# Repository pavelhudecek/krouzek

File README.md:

Na práci s GITem si nainstalujte
    https://git-scm.com/downloads/win

Když už máte git nainstalován,
1. Založte si nějaký adresář, kam se bude repozitář z gitu klonovat, např. C:\Users\mojejmeno\Documents\git-krouzek-elektro
2. Otevřete příkazový terminál, pokud ho nemáte už přidanej ve start menu, dejte hledat cmd.
3. Příkazem cd jít do toho adresáře:
   cd C:\Users\mojejmeno\Documents\git-krouzek-elektro (a stisk enter)
4. git clone https://github.com/pavelhudecek/krouzek.git (a stisk enter)

Microchip Studio a jak začít:
https://dejvice.cz/edison/krouzek/at-st/

Kromě Microchip Studia můžete použít třeba VScode:
https://code.visualstudio.com/download
Ale je poněkud univerzálnější, takže je potřeba doinstalovat vhodné pluginy a podobně.

Na nahrávání programu bez Microchip Studia použijte např.:
https://blog.zakkemble.net/avrdudess-a-gui-for-avrdude/

Nebo si můžete do VScode nastavit nahrávání přes avrdude:
    https://github.com/mariusgreuel/avrdude/releases 

Dále je dobré si pořídit terminál pro komunikaci. V nejhorším se dá použít i integrovaný v Microchip Studiu, ale radši třeba YAT:
    https://sourceforge.net/projects/y-a-terminal/
    V některých projektech najdete soubor s příponou .yat, tam je nastavení pro daný projekt, stačí nahrát, jen bude asi potřeba změnit číslo portu.

Poznámka: Na kroužku to vypadalo, že z Microchip Studia nejde nahrávat program přes Xnano416 do ATtiny814, ale zdá se, že se jedná jen o větší citlivost na běžící repráček, nebo rychlý blikání. Jinak to normálně jde:-)

https://dejvice.cz/edison/tmp/ibom.html

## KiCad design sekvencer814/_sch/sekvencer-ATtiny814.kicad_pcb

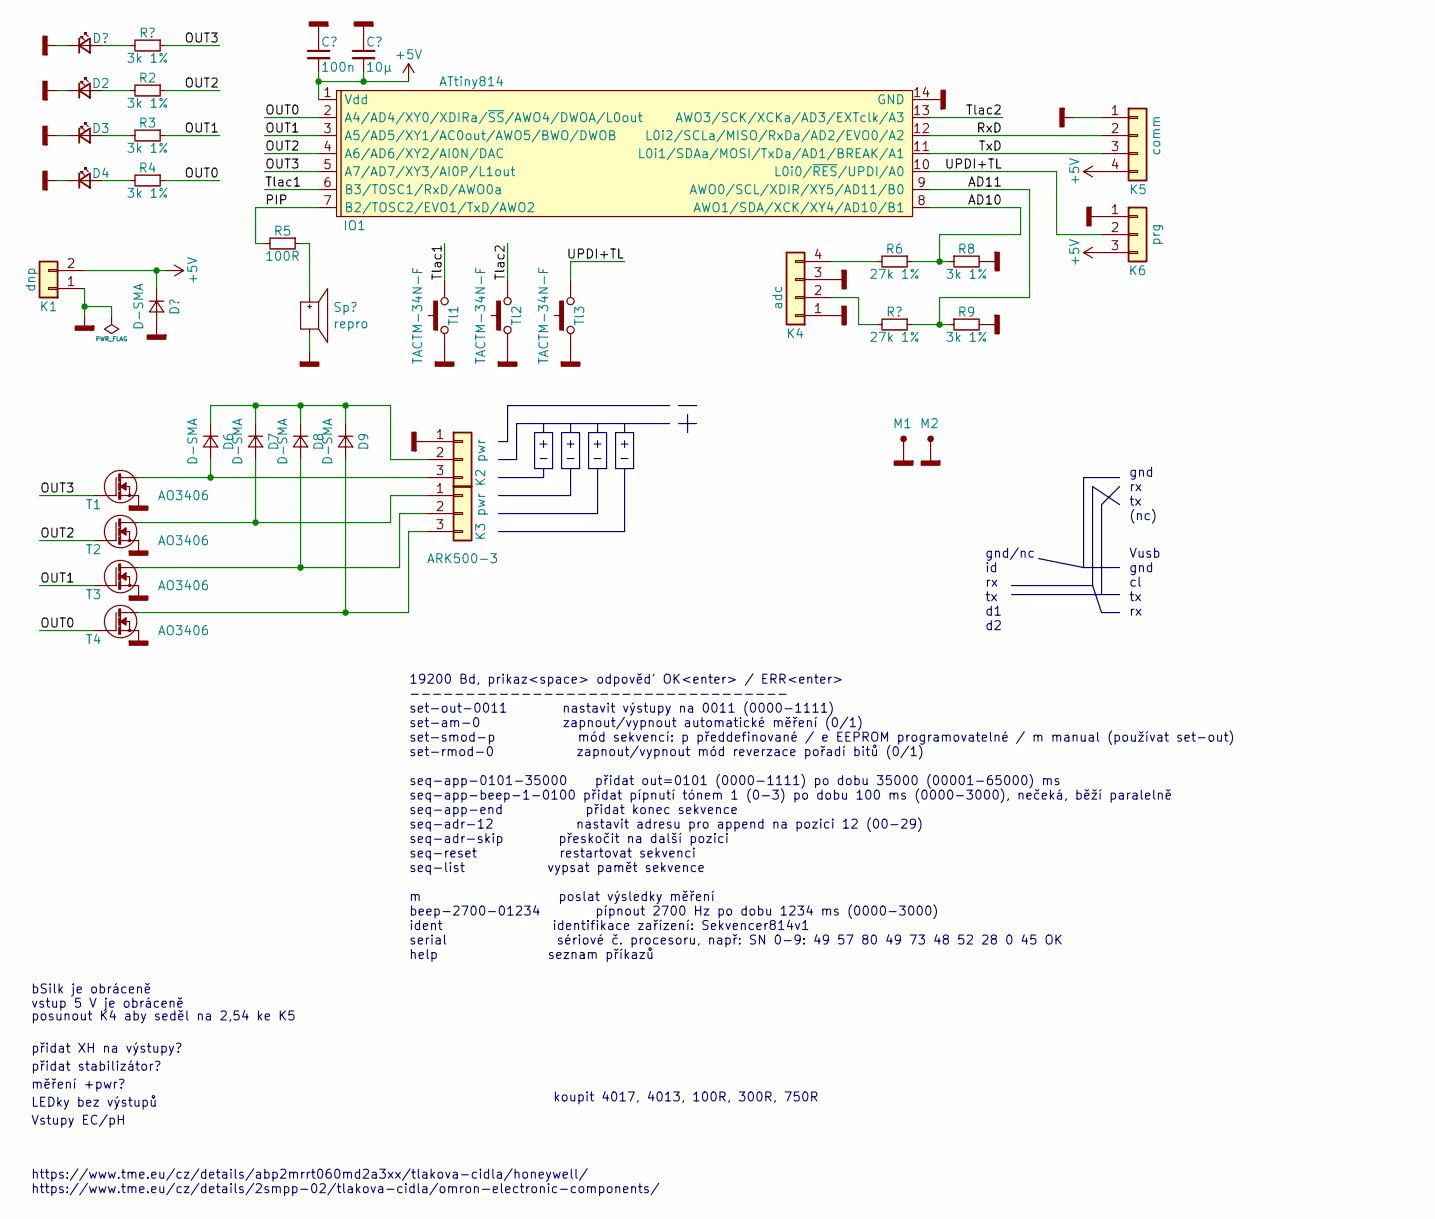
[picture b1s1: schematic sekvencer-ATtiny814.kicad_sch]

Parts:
C1: 100n; R_1206-hand
C2: 10µ; R_1206-hand
D1, D2, D3, D4: R; LED1206-hand
D5, D6, D7, D8, D9: D-SMA; D-SMA-hand
IO1: ATtiny814; SO14-hand
K1: dnp; kon-1x2-s2x4+holes-pwr
K2, K3: ARK500-3
K4, K5: dnp; kon-1x4-D1-1,7
K6: dnp; kon-1x3_P2.54_Vertical
M1, M2: dnp; PTH-M3-7.5
R1, R2, R3, R4, R8, R9: 3k 1%; R_1206-hand
R5: 100R; R_1206-hand
R6, R7: 27k 1%; R_1206-hand
Sp1: repro; repro-D12-RM6.5-pol
T1, T2, T3, T4: AO3406; SOT23-hand
Tl1, Tl2, Tl3: TACTM-34N-F; TD-03-hand

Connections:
+5V: C1.2, C2.2, D5.1 (K), IO1.1 (Vdd), K1.2, K5.4, K6.3
/AD10: IO1.8 (AWO1/SDA/XCK/XY4/AD10/B1), R6.1, R8.1
/AD11: IO1.9 (AWO0/SCL/XDIR/XY5/AD11/B0), R7.1, R9.1
/OUT0: IO1.2 (A4/AD4/XY0/XDIRa/~SS/AWO4/DWOA/L0out), R4.1, T4.1 (G)
/OUT1: IO1.3 (A5/AD5/XY1/AC0out/AWO5/BWO/DWOB), R3.1, T3.1 (G)
/OUT2: IO1.4 (A6/AD6/XY2/AI0N/DAC), R2.1, T2.1 (G)
/OUT3: IO1.5 (A7/AD7/XY3/AI0P/L1out), R1.1, T1.1 (G)
/PIP: IO1.7 (B2/TOSC2/EVO1/TxD/AWO2), R5.2
/RxD: IO1.12 (L0i2/SCLa/MISO/RxDa/AD2/EVO0/A2), K5.2
/Tlac1: IO1.6 (B3/TOSC1/RxD/AWO0a), Tl1.2
/Tlac2: IO1.13 (AWO3/SCK/XCKa/AD3/EXTclk/A3), Tl2.2
/TxD: IO1.11 (L0i1/SDAa/MOSI/TxDa/AD1/BREAK/A1), K5.3
/UPDI+TL: IO1.10 (L0i0/~RES/UPDI/A0), K6.2, Tl3.2
GNDD: C1.1, C2.1, D1.1 (K), D2.1 (K), D3.1 (K), D4.1 (K), D5.2 (A), IO1.14 (GND), K1.1, K2.1, K4.1, K4.3, K5.1, K6.1, M1.1 (TP), M2.1 (TP), R8.2, R9.2, Sp1.2 (m), T1.2 (S), T2.2 (S), T3.2 (S), T4.2 (S), Tl1.1, Tl2.1, Tl3.1
unnamed: D1.2 (A), R1.2
unnamed: D2.2 (A), R2.2
unnamed: D3.2 (A), R3.2
unnamed: D4.2 (A), R4.2
unnamed: D6.2 (A), K2.3, T1.3 (D)
unnamed: D6.1 (K), D7.1 (K), D8.1 (K), D9.1 (K), K2.2
unnamed: D7.2 (A), K3.1, T2.3 (D)
unnamed: D8.2 (A), K3.2, T3.3 (D)
unnamed: D9.2 (A), K3.3, T4.3 (D)
unnamed: K4.2, R7.2
unnamed: K4.4, R6.2
unnamed: R5.1, Sp1.1 (p)

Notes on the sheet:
+ -
gnd rx tx (nc)
https://www.tme.eu/cz/details/abp2mrrt060md2a3xx/tlakova-cidla/honeywell/ https://www.tme.eu/cz/details/2smpp-02/tlakova-cidla/omron-electronic-components/
koupit 4017, 4013, 100R, 300R, 750R
vstup 5 V je obráceně
bSilk je obráceně
Vstupy EC/pH
přidat XH na výstupy?
LEDky bez výstupů
Vusb gnd cl tx rx
gnd/nc id rx tx d1 d2
přidat stabilizátor?
posunout K4 aby seděl na 2,54 ke K5
19200 Bd, prikaz<space> odpověď OK<enter> / ERR<enter> ---------------------------------- set-out-0011 nastavit výstupy na 0011 (0000-1111) set-am-0 zapnout/vypnout automatické měření (0/1) set-smod-p mód sekvencí: p předdefinované / e EEPROM programovatelné / m manual (používat set-out) set-rmod-0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
měření +pwr?

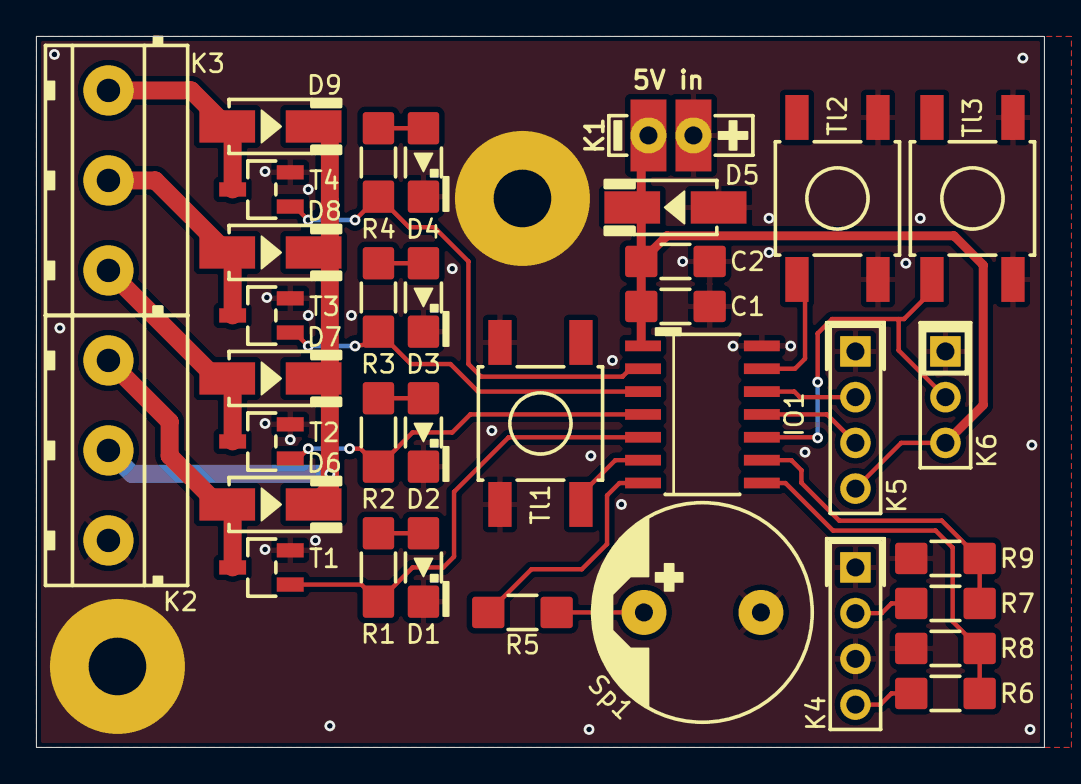
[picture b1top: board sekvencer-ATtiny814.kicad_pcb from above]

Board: 2 copper layers, 56.0 x 39.5 mm, 37 parts (0 on the bottom side), 26 nets.

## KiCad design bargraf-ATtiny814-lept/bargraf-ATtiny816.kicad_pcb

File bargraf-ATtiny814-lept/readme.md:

Kicad schéma + DPS
https://www.kicad.org/download/windows/

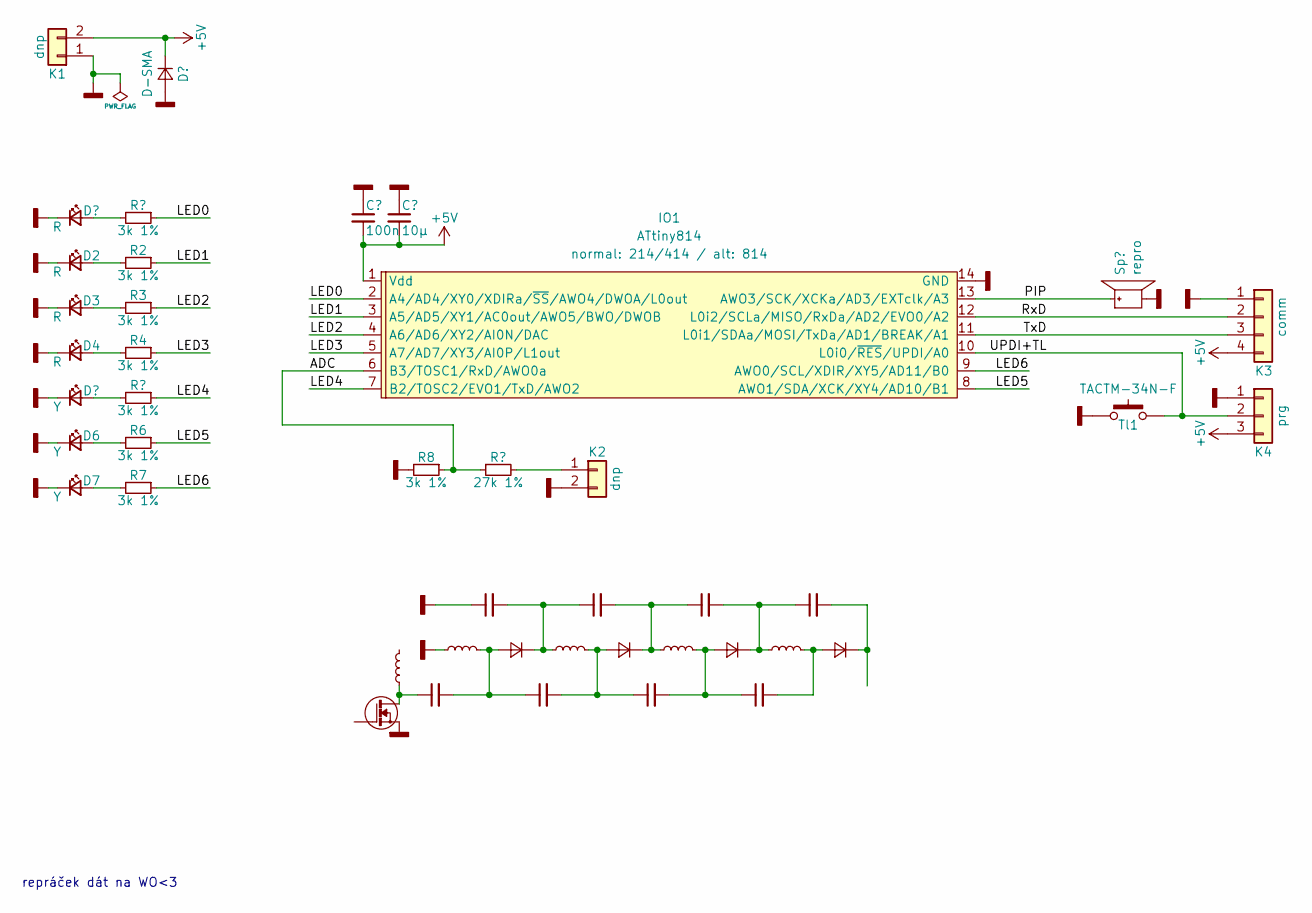
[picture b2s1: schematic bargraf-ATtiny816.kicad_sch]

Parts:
C1: 100n; R_1206-hand
C2: 10µ; R_1206-hand
D1, D2, D3, D4: R; LED1206-hand
D5, D6, D7: Y; LED1206-hand
D8: D-SMA; D-SMA-hand
IO1: ATtiny814; SO14
K1, K2: dnp; kon-1x2-s2x4
K3: dnp; kon-1x4-s1,2x3-P2
K4: dnp; kon-1x3-s2x4
R1, R2, R3, R4, R5, R6, R7, R8: 3k 1%; R_1206-hand
R9: 27k 1%; R_1206-hand
Sp1: repro; repro-D12-RM6.5-pol
Tl1: TACTM-34N-F; TD-03-hand

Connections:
+5V: C1.2, C2.2, D8.1 (K), IO1.1 (Vdd), K1.2, K3.4, K4.3
/ADC: IO1.6 (B3/TOSC1/RxD/AWO0a), R8.1, R9.1
/LED0: IO1.2 (A4/AD4/XY0/XDIRa/~SS/AWO4/DWOA/L0out), R1.1
/LED1: IO1.3 (A5/AD5/XY1/AC0out/AWO5/BWO/DWOB), R2.1
/LED2: IO1.4 (A6/AD6/XY2/AI0N/DAC), R3.1
/LED3: IO1.5 (A7/AD7/XY3/AI0P/L1out), R4.1
/LED4: IO1.7 (B2/TOSC2/EVO1/TxD/AWO2), R5.1
/LED5: IO1.8 (AWO1/SDA/XCK/XY4/AD10/B1), R6.1
/LED6: IO1.9 (AWO0/SCL/XDIR/XY5/AD11/B0), R7.1
/PIP: IO1.13 (AWO3/SCK/XCKa/AD3/EXTclk/A3), Sp1.1 (p)
/RxD: IO1.12 (L0i2/SCLa/MISO/RxDa/AD2/EVO0/A2), K3.2
/TxD: IO1.11 (L0i1/SDAa/MOSI/TxDa/AD1/BREAK/A1), K3.3
/UPDI+TL: IO1.10 (L0i0/~RES/UPDI/A0), K4.2, Tl1.2
GNDD: C1.1, C2.1, D1.1 (K), D2.1 (K), D3.1 (K), D4.1 (K), D5.1 (K), D6.1 (K), D7.1 (K), D8.2 (A), IO1.14 (GND), K1.1, K2.2, K3.1, K4.1, R8.2, Sp1.2 (m), Tl1.1
unnamed: D1.2 (A), R1.2
unnamed: D2.2 (A), R2.2
unnamed: D3.2 (A), R3.2
unnamed: D4.2 (A), R4.2
unnamed: D5.2 (A), R5.2
unnamed: D6.2 (A), R6.2
unnamed: D7.2 (A), R7.2
unnamed: K2.1, R9.2

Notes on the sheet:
repráček dát na WO<3

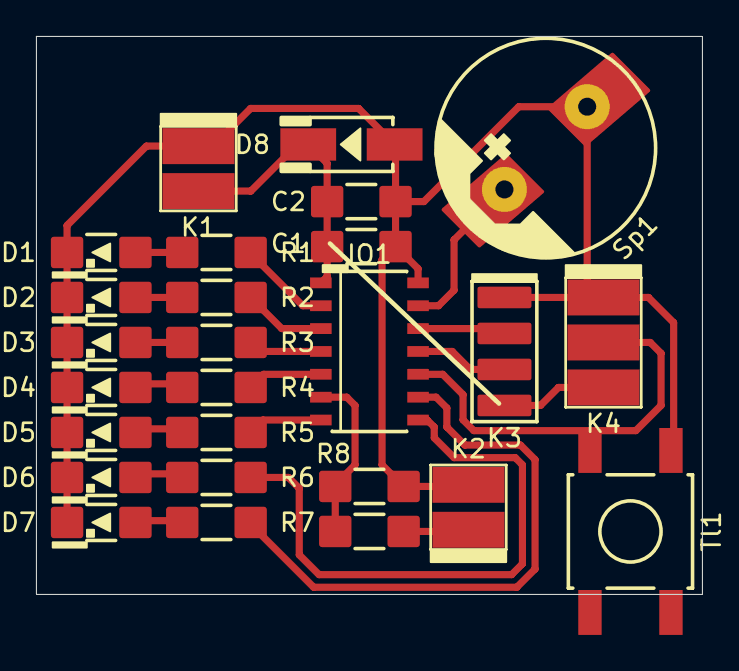
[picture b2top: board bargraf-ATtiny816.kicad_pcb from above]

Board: 2 copper layers, 37.0 x 31.0 mm, 26 parts (0 on the bottom side), 22 nets.

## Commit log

2025-03-08 zvuky
2025-03-09 zvuky funkcni
2025-05-11 Sekvencer Tiny814 v1.0 2025
